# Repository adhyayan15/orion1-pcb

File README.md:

# Orion-1

### My first attempt at designing a robotics controller from scratch

I wanted a controller I could eventually use in my own robots instead of building every project around a development board and a mess of jumper wires. That's where Orion-1 started.

The plan was to put the essentials on one PCB: an STM32, motor control, servo connections, power regulation, and enough headers to plug in sensors later. I built the schematic and laid out the board in KiCad. It's a 4 × 4-inch, two-layer design based around the **STM32F407VGTx**.

This is **revision one**, not a finished commercial controller. Some functional issues are still unresolved, and I haven't documented a successful full hardware bring-up. I'm keeping it here because the design process itself taught me a lot.

## What's on the board?

| Part | Why it's there |
| --- | --- |
| STM32F407VGTx | Main microcontroller; an Arm Cortex-M4 |
| TB6612FNG | Dual DC-motor driver |
| AP2112K-3.3 | 3.3 V regulation for the logic side |
| USB-C connector + polyfuse | Part of the input/power interface |
| Four servo headers | Connections for future actuators |
| UART, I²C, SPI and sensor headers | Room to add peripherals |
| SWD signals, reset, oscillator, LEDs | Bring-up, debugging and basic feedback |

The KiCad project uses a **101.6 × 101.6 mm**, two-copper-layer board outline, with 1.6 mm nominal thickness.

## A closer look

| PCB layout | Schematic |
| :---: | :---: |
|  |  |

## What I learned building it

The parts list was the easy part. Getting all those parts to make sense together was harder.

I spent time sorting out KiCad's power flags and ERC messages, thinking through the USB supply path, checking crystal connections, and fixing grounding and routing issues. A robotics board also forces you to think about things you can mostly ignore on a breadboard: motor current, where the return paths go, and whether your connectors will actually be usable after assembly.

One thing I would do differently is plan the bring-up process earlier, before worrying so much about making the layout look finished. A routed board isn't the same thing as a tested board.

## Current state

The repository includes the [editable KiCad project](KiCad/), exported Gerber layers, and the images above. **It's still a design-stage prototype.** I haven't included firmware, measured rail voltages, or a verified motor/servo demo. The current repository also doesn't have NC drill output, so the manufacturing package needs to be regenerated before ordering.

If you're looking through the design, the most useful files are:

- [Schematic](KiCad/orion-1.kicad_sch) and [PCB layout](KiCad/orion-1.kicad_pcb)
- [Hardware notes](docs/HARDWARE_ARCHITECTURE.md)
- [Bring-up checklist](docs/BRING_UP_AND_VALIDATION.md)
- [Fabrication notes](docs/FABRICATION_NOTES.md)

## What's next

I want to resolve the electrical issues, verify the 3.3 V supply and SWD connection, flash a basic LED test, and then move on to peripherals and motor control. Once I can show actual measurements and a running board, I'll add them here rather than just calling the design “working.”

---

Built by **Adhyayan Tiwari** · [MIT License](LICENSE)

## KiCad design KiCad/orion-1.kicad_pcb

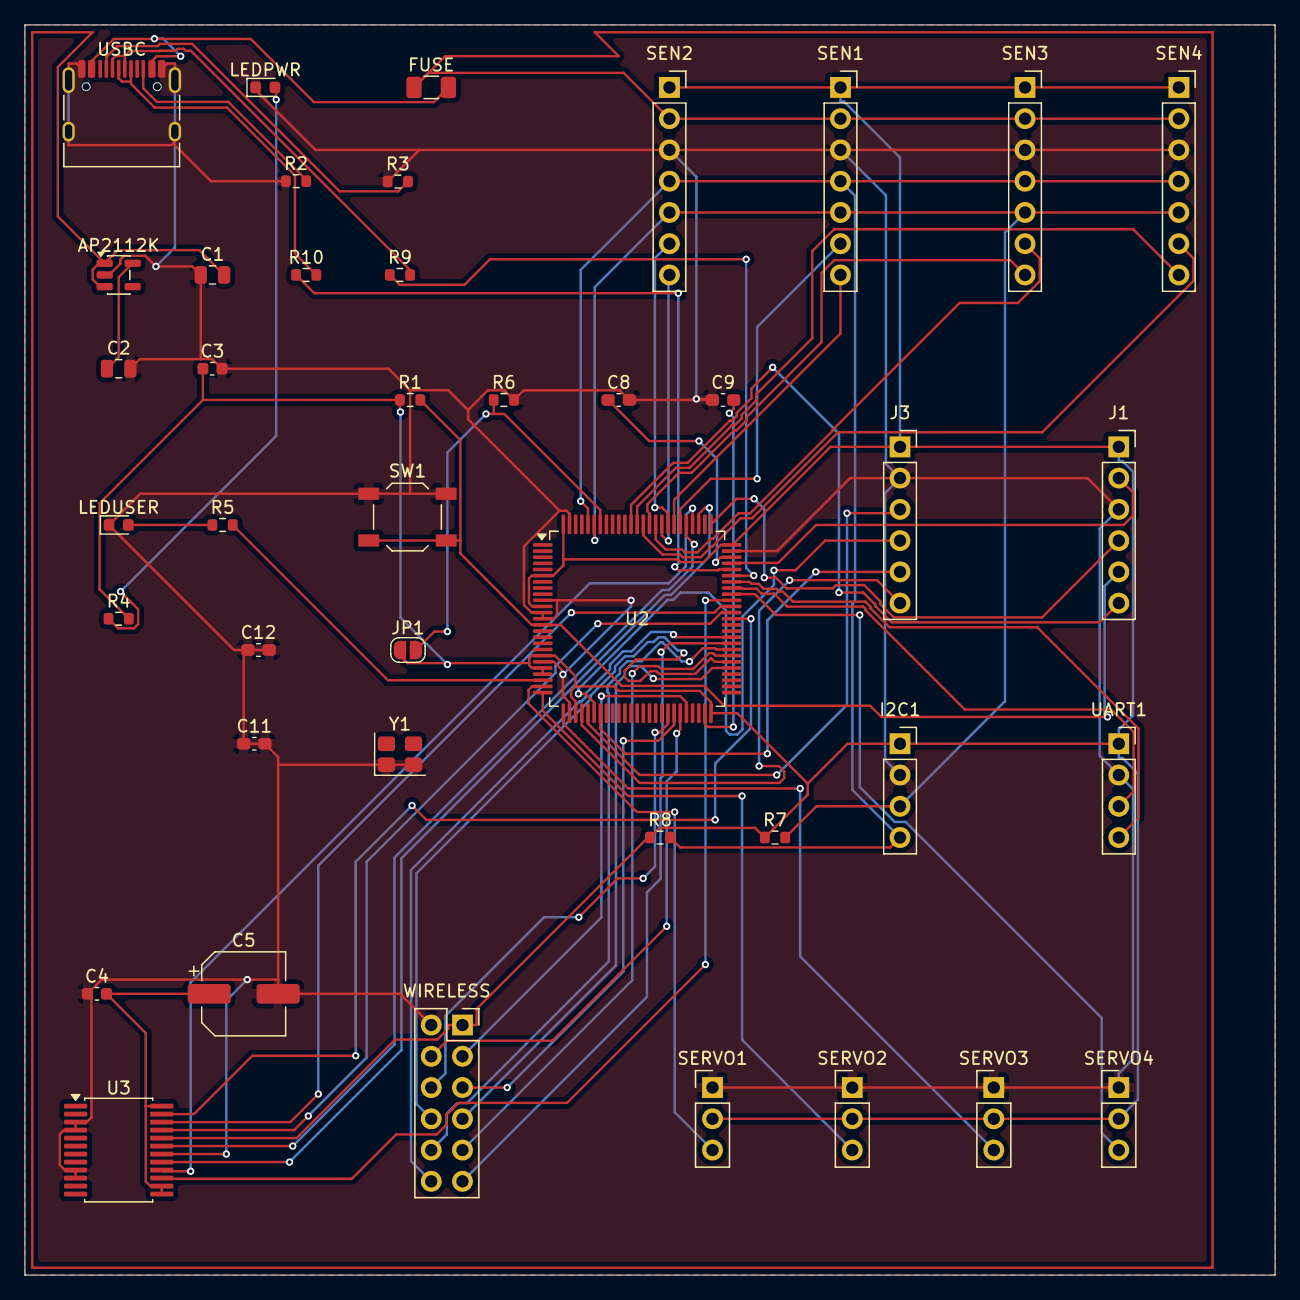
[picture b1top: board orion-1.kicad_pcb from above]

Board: 2 copper layers, 101.6 x 101.6 mm, 42 parts (0 on the bottom side), 59 nets.

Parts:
AP2112K: AP2112K-3.3; SOT-23-5
C1, C2: 10uF; C_0805_2012Metric
C3, C4: 100nF; C_0603_1608Metric
C5: 100uF; CP_Elec_6.3x5.4
C8, C9: 2.2uF; C_0603_1608Metric_Pad1.08x0.95mm_HandSolder
C11, C12: 22pF; C_0603_1608Metric_Pad1.08x0.95mm_HandSolder
FUSE: Polyfuse; Fuse_1206_3216Metric
I2C1: PinSocket_1x04_P2.54mm_Vertical
J1: Conn_01x06; PinSocket_1x06_P2.54mm_Vertical
J3: SPI1; PinSocket_1x06_P2.54mm_Vertical
JP1: Jumper_2_Open; SolderJumper-2_P1.3mm_Open_RoundedPad1.0x1.5mm
LEDPWR: LEDPWR; LED_0603_1608Metric
LEDUSER: LEDUSER; LED_0603_1608Metric
R1: 10k; R_0603_1608Metric
R2, R3: 5.1k; R_0603_1608Metric
R4, R5: 330; R_0603_1608Metric
R6: 10000; R_0603_1608Metric
R7, R8: 4.7k; R_0603_1608Metric
R9, R10: 22; R_0603_1608Metric
SEN1: SEN1; PinSocket_1x07_P2.54mm_Vertical
SEN2: SEN2; PinSocket_1x07_P2.54mm_Vertical
SEN3: SEN3; PinSocket_1x07_P2.54mm_Vertical
SEN4: SEN4; PinSocket_1x07_P2.54mm_Vertical
SERVO1, SERVO2, SERVO3, SERVO4: Conn_01x03; PinHeader_1x03_P2.54mm_Vertical
SW1: SW_Push; SW_SPST_TL3342
U2: STM32F407VGTx; LQFP-100_14x14mm_P0.5mm
U3: TB6612FNG; SSOP-24_5.3x8.2mm_P0.65mm
UART1: PinSocket_1x04_P2.54mm_Vertical
USBC: USB_C_Receptacle_USB2.0_16P; USB_C_Receptacle_HRO_TYPE-C-31-M-12
WIRELESS: WIRELESS PORT; PinSocket_2x06_P2.54mm_Vertical
Y1: Crystal; Crystal_SMD_3225-4Pin_3.2x2.5mm

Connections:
+3.3V: C3.1, I2C1.1, J1.1, J3.1, JP1.1 (A), R1.1, R4.2, R7.1, R8.1, SEN1.1, SEN2.1, SEN3.1, SEN4.1, SERVO1.2, SERVO2.2, SERVO3.2, SERVO4.2, U2.6 (VBAT), U2.11 (VDD), U2.19 (VDD), U2.21 (VREF+), U2.22 (VDDA), U2.28 (VDD), U2.50 (VDD), U2.75 (VDD), U2.100 (VDD), U3.20 (VCC), UART1.1, WIRELESS.1
/AIN1: U2.64 (PC7), U3.21 (AIN1)
/AIN2: U2.65 (PC8), U3.22 (AIN2)
/BIN1: U2.78 (PC10), U3.17 (BIN1)
/BIN2: U2.79 (PC11), U3.16 (BIN2)
/CHIP-SEL: J3.6, U2.29 (PA4)
/CS2: U2.43 (PE12), WIRELESS.6
/MISO: J3.4, U2.31 (PA6)
/MISO2: U2.45 (PE14), WIRELESS.4
/MOSI: J3.5, U2.32 (PA7)
/MOSI2: U2.46 (PE15), WIRELESS.3
/MOTOR_EN: U2.80 (PC12), U3.19 (STBY)
/MOTOR_VCC: C4.2, C5.1, U3.13 (VM2), U3.14 (VM3), U3.24 (VM1)
/PA0: R5.2, U2.23 (PA0)
/PA1: SERVO1.3, U2.24 (PA1)
/PA2: SERVO2.3, U2.25 (PA2)
/PA3: SERVO3.3, U2.26 (PA3)
/PA8: SERVO4.3, U2.67 (PA8)
/PA11: R9.1, U2.70 (PA11)
/PA12: R10.1, U2.71 (PA12)
/PWMA: U2.63 (PC6), U3.23 (PWMA)
/PWMB: U2.66 (PC9), U3.15 (PWMB)
/RECIEVER: U2.69 (PA10), UART1.4
/RESET: J1.5, R1.2, SW1.2, U2.14 (NRST)
/SCK: J3.3, U2.30 (PA5)
/SCK2: U2.44 (PE13), WIRELESS.5
/SCL: I2C1.3, R7.2, SEN1.5, SEN2.5, SEN3.5, SEN4.5, U2.95 (PB8)
/SDA: I2C1.4, R8.2, SEN1.4, SEN2.4, SEN3.4, SEN4.4, U2.96 (PB9)
/SEN101: SEN1.6, U2.81 (PD0)
/SEN102: SEN1.7, U2.82 (PD1)
/SEN201: SEN2.6, U2.83 (PD2)
/SEN202: SEN2.7, U2.84 (PD3)
/SEN301: SEN3.6, U2.85 (PD4)
/SEN302: SEN3.7, U2.86 (PD5)
/SEN401: SEN4.6, U2.87 (PD6)
/SEN402: SEN4.7, U2.88 (PD7)
/SWCLK: J1.4, U2.76 (PA14)
/SWDIO: J1.2, U2.72 (PA13)
/SWO: J1.6, U2.89 (PB3)
/TRANSM: U2.68 (PA9), UART1.3
/UART_REC: U2.59 (PD12), WIRELESS.11
/UART_TRAN: U2.58 (PD11), WIRELESS.10
/USB5V: AP2112K.1 (VIN), AP2112K.3 (EN), C1.2, FUSE.1, SEN1.2, SEN2.2, SEN3.2, SEN4.2
/WIFI_EN: U2.56 (PD9), WIRELESS.8
/WIFI_GPIO: U2.60 (PD13), WIRELESS.12
/WIFI_INTR: U2.57 (PD10), WIRELESS.9
/WIFI_RST: U2.55 (PD8), WIRELESS.7
GND: AP2112K.2 (GND), C1.1, C2.2, C3.2, C4.1, C5.2, C8.2, C9.1, C11.1, C11.2, C12.1, C12.2, I2C1.2, J1.3, J3.2, LEDPWR.1 (K), LEDUSER.1 (K), R2.1, R3.1, R6.2, SEN1.3, SEN2.3, SEN3.3, SEN4.3, SERVO1.1, SERVO2.1, SERVO3.1, SERVO4.1, SW1.1, U2.10 (VSS), U2.12 (PH0), U2.13 (PH1), U2.20 (VSSA), U2.27 (VSS), U2.74 (VSS), U2.99 (VSS), U3.3 (PGND1), U3.4 (PGND1), U3.9 (PGND2), U3.10 (PGND2), U3.18 (GND), UART1.2, USBC.A1 (GND), USBC.A12 (GND), USBC.B1 (GND), USBC.B12 (GND), USBC.SH (SHIELD), WIRELESS.2, Y1.1, Y1.2
unnamed: LEDPWR.2 (A), R4.1
unnamed: LEDUSER.2 (A), R5.1
unnamed: FUSE.2, USBC.A4 (VBUS), USBC.A9 (VBUS), USBC.B4 (VBUS), USBC.B9 (VBUS)
unnamed: R3.2, USBC.A5 (CC1)
unnamed: R2.2, USBC.B5 (CC2)
unnamed: R10.2, USBC.A6 (D+), USBC.B6 (D+)
unnamed: R9.2, USBC.A7 (D-), USBC.B7 (D-)
unnamed: JP1.2 (B), R6.1, U2.94 (BOOT0)
unnamed: AP2112K.5 (VOUT), C2.1
unnamed: C9.2, U2.49 (VCAP_1)
unnamed: C8.1, U2.73 (VCAP_2)
